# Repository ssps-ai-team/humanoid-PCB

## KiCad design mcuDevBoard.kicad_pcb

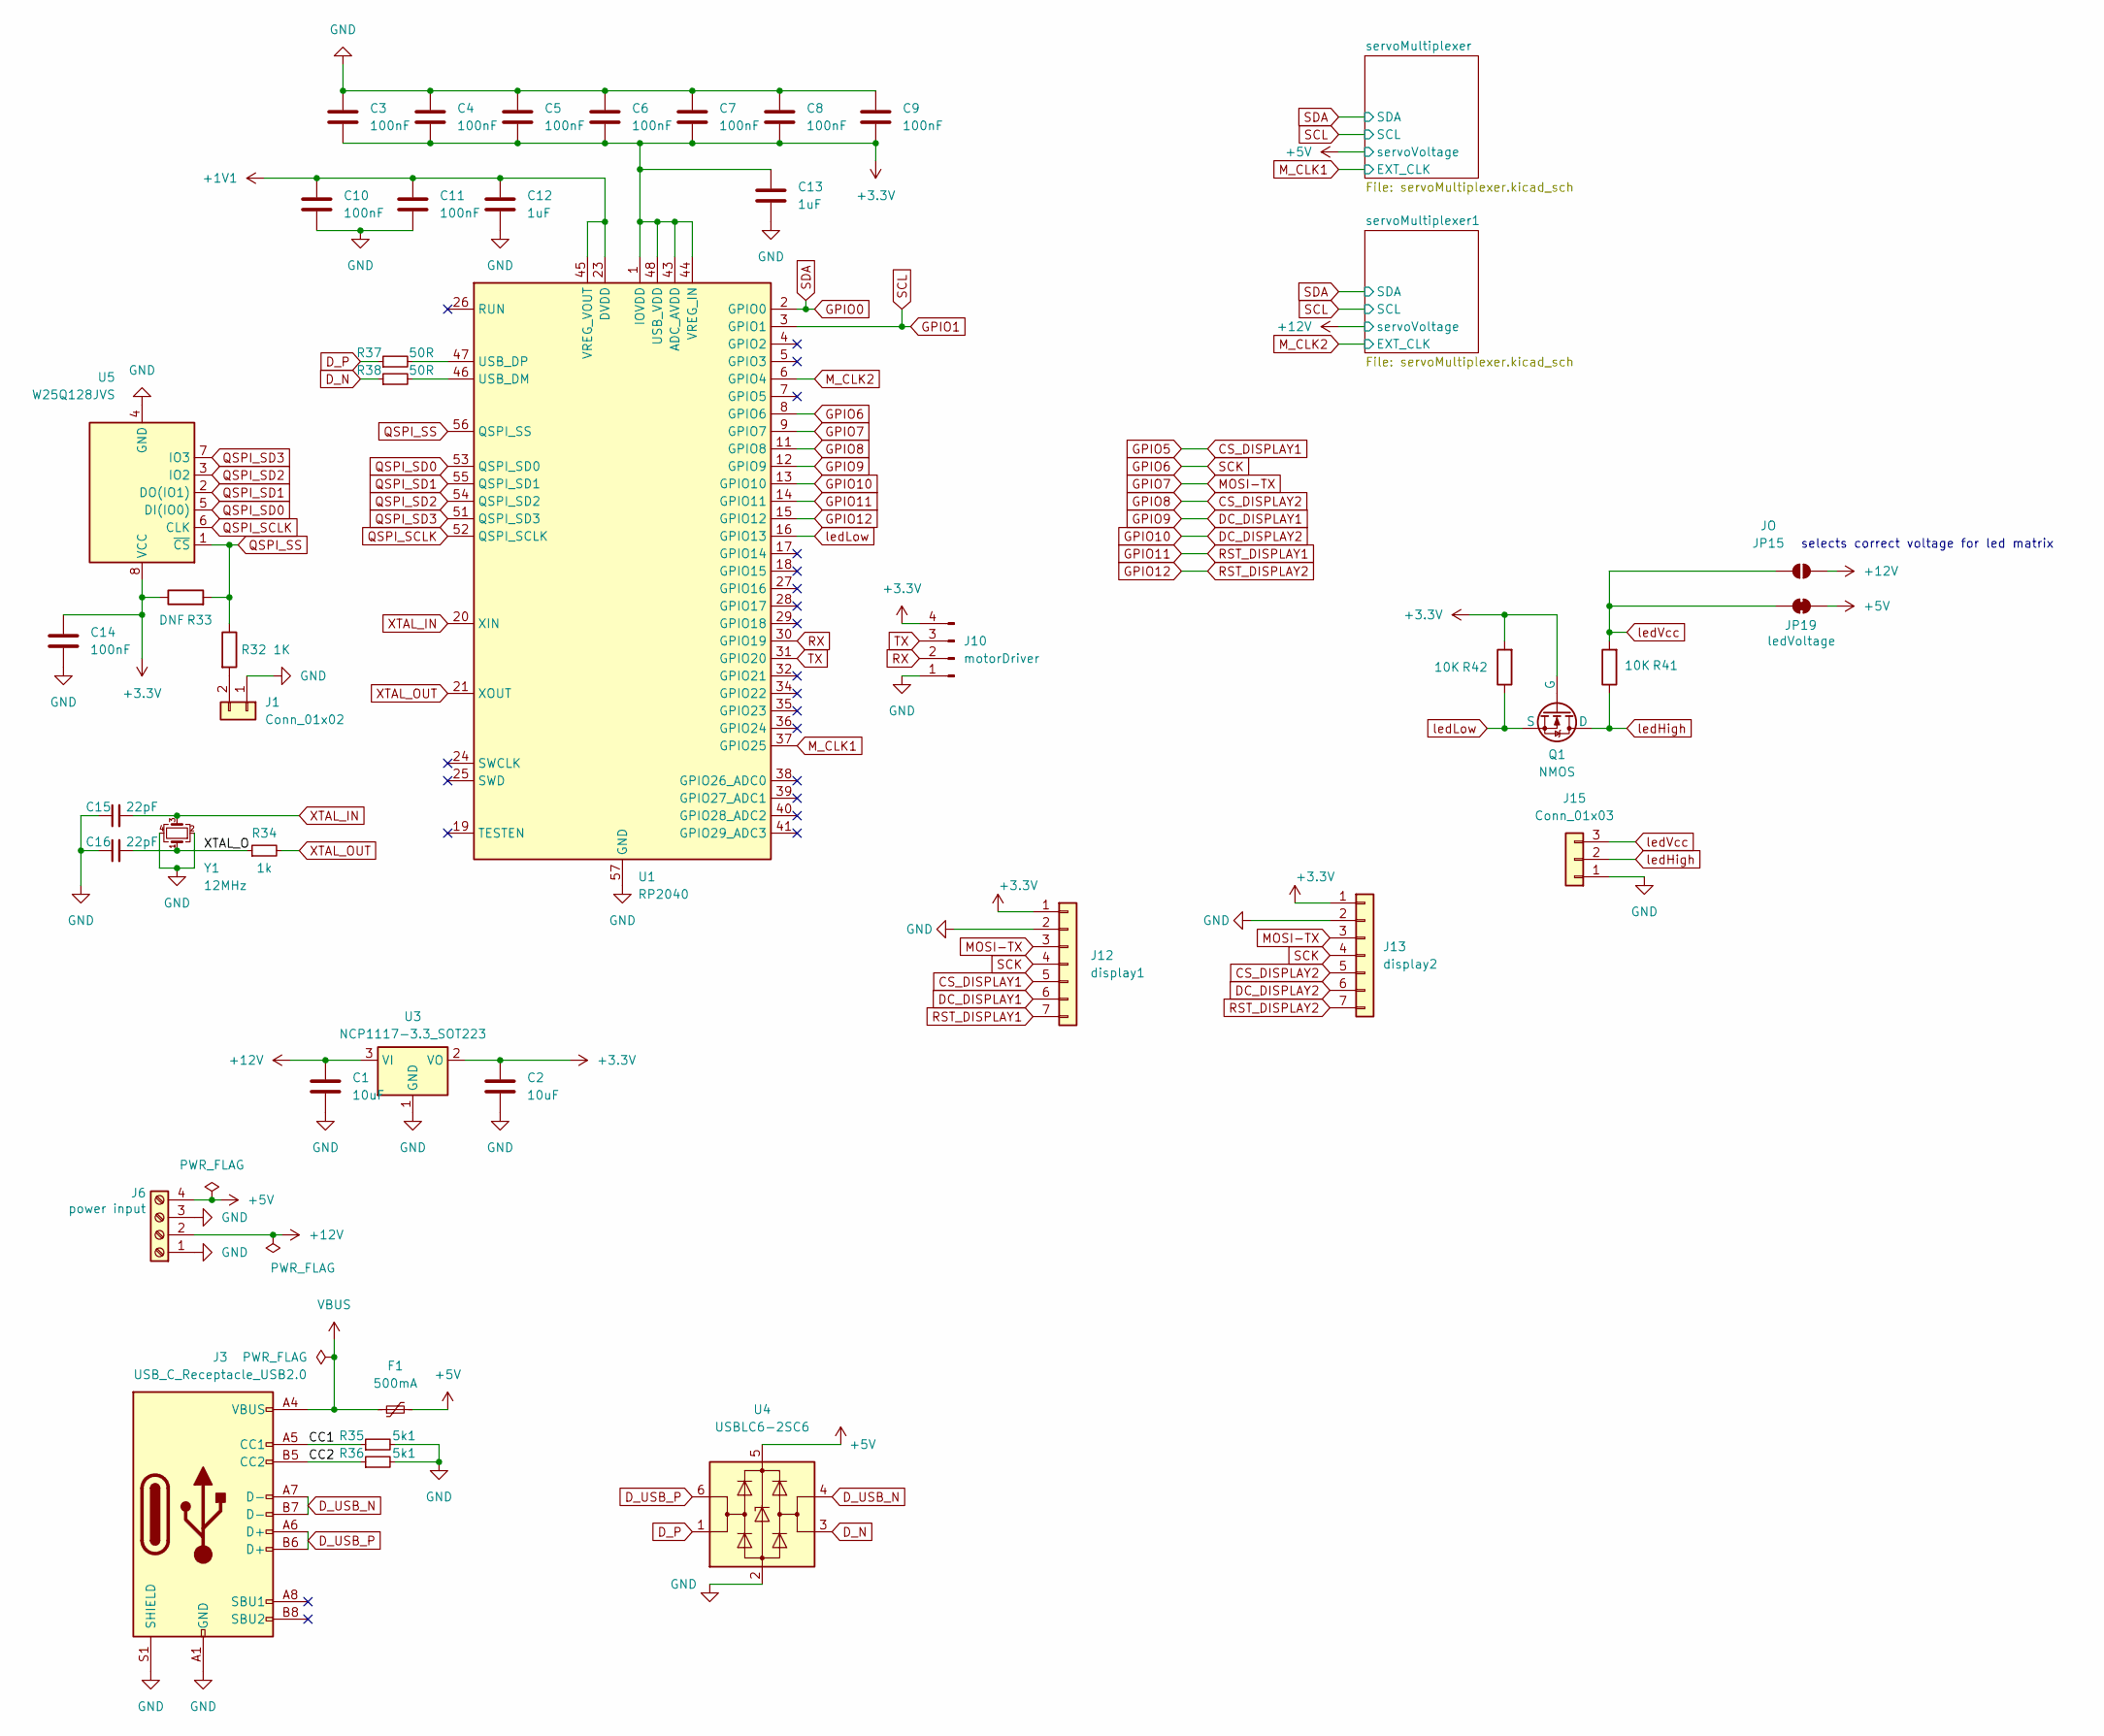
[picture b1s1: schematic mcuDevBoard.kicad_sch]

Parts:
C1, C2: 10uF; C_1206_3216Metric_Pad1.33x1.80mm_HandSolder
C3, C4, C5, C6, C7, C8, C9, C10, C11, C14: 100nF; C_0805_2012Metric_Pad1.18x1.45mm_HandSolder
C12, C13: 1uF; C_0805_2012Metric_Pad1.18x1.45mm_HandSolder
C15, C16: 22pF; C_0805_2012Metric_Pad1.18x1.45mm_HandSolder; LCSC C1555
F1: 500mA; Fuse_1206_3216Metric; LCSC C70076
J1: Conn_01x02; PinSocket_1x02_P2.54mm_Vertical
J3: USB_C_Receptacle_USB2.0; USB_C_Receptacle_HRO_TYPE-C-31-M-12; LCSC C165948
J6: power input; CONN-TH_4P-P7.50_DIBO_DB128V-7.5-4P-GN-S
J10: motorDriver; PinHeader_1x04_P2.54mm_Vertical
J12: display1; PinHeader_1x07_P2.54mm_Vertical
J13: display2; PinHeader_1x07_P2.54mm_Vertical
J15: Conn_01x03; PinSocket_1x03_P2.54mm_Vertical
JP15: JO; SolderJumper-2_P1.3mm_Open_RoundedPad1.0x1.5mm
JP19: ledVoltage; SolderJumper-2_P1.3mm_Bridged_RoundedPad1.0x1.5mm
Q1: NMOS; SOT-23_Handsoldering
R32: 1K; R_1206_3216Metric_Pad1.30x1.75mm_HandSolder
R33: DNF; R_1206_3216Metric_Pad1.30x1.75mm_HandSolder
R34: 1k; R_1206_3216Metric_Pad1.30x1.75mm_HandSolder; LCSC C11702
R35, R36: 5k1; R_1206_3216Metric_Pad1.30x1.75mm_HandSolder; LCSC C25905
R37, R38: 50R; C_0805_2012Metric; LCSC C25190
R41, R42: 10K; R_1206_3216Metric_Pad1.30x1.75mm_HandSolder
U1: RP2040; QFN-56-1EP_7x7mm_P0.4mm_EP3.2x3.2mm
U3: NCP1117-3.3_SOT223; SOT-223-3_TabPin2
U4: USBLC6-2SC6; SOT-23-6; LCSC C2827654
U5: W25Q128JVS; SOIC-8_5.23x5.23mm_P1.27mm
Y1: 12MHz; Crystal_SMD_3225-4Pin_3.2x2.5mm; LCSC C9002

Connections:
+1V1: C10.1, C11.1, C12.1, U1.23 (DVDD), U1.45 (VREG_VOUT), U1.50 (DVDD)
+3.3V: C2.1, C3.2, C4.2, C5.2, C6.2, C7.2, C8.2, C9.2, C13.1, C14.1, J10.4, J12.1, J13.1, Q1.2 (G), R33.1, R42.2, U1.1 (IOVDD), U1.10 (IOVDD), U1.22 (IOVDD), U1.33 (IOVDD), U1.42 (IOVDD), U1.43 (ADC_AVDD), U1.44 (VREG_IN), U1.48 (USB_VDD), U1.49 (IOVDD), U3.2 (VO), U5.8 (VCC); also elsewhere on the board
+5V: F1.2, J6.4, JP19.1 (A), U4.5 (VBUS); also elsewhere on the board
+12V: C1.1, J6.2, JP15.1 (A), U3.3 (VI); also elsewhere on the board
/CC1: J3.A5 (CC1), R35.1
/CC2: J3.B5 (CC2), R36.1
/XTAL_O: C16.2, R34.1, Y1.1
CS_DISPLAY1: J12.5
CS_DISPLAY2: J13.5, U1.11 (GPIO8)
DC_DISPLAY1: J12.6, U1.12 (GPIO9)
DC_DISPLAY2: J13.6, U1.13 (GPIO10)
D_N: R38.1, U4.3 (I/O2)
D_P: R37.1, U4.1 (I/O1)
D_USB_N: J3.A7 (D-), J3.B7 (D-), U4.4 (I/O2)
D_USB_P: J3.A6 (D+), J3.B6 (D+), U4.6 (I/O1)
GND: C1.2, C2.2, C3.1, C4.1, C5.1, C6.1, C7.1, C8.1, C9.1, C10.2, C11.2, C12.2, C13.2, C14.2, C15.1, C16.1, J1.1, J3.A1 (GND), J3.A12 (GND), J3.B1 (GND), J3.B12 (GND), J3.S1 (SHIELD), J6.1, J6.3, J10.1, J12.2, J13.2, J15.1, R35.2, R36.2, U1.57 (GND), U3.1 (GND), U4.2 (GND), U5.4 (GND), Y1.2, Y1.4; also elsewhere on the board
GPIO0: U1.2 (GPIO0); also elsewhere on the board
GPIO1: U1.3 (GPIO1); also elsewhere on the board
GPIO6: J12.4, J13.4, U1.8 (GPIO6)
GPIO7: J12.3, J13.3, U1.9 (GPIO7)
GPIO11: J12.7, U1.14 (GPIO11)
GPIO12: J13.7, U1.15 (GPIO12)
M_CLK1: U1.37 (GPIO25); also elsewhere on the board
M_CLK2: U1.6 (GPIO4); also elsewhere on the board
unnamed: J1.2, R32.2
unnamed: R38.2, U1.46 (USB_DM)
unnamed: R37.2, U1.47 (USB_DP)
QSPI_SCLK: U1.52 (QSPI_SCLK), U5.6 (CLK)
QSPI_SD0: U1.53 (QSPI_SD0), U5.5 (DI(IO0))
QSPI_SD1: U1.55 (QSPI_SD1), U5.2 (DO(IO1))
QSPI_SD2: U1.54 (QSPI_SD2), U5.3 (IO2)
QSPI_SD3: U1.51 (QSPI_SD3), U5.7 (IO3)
QSPI_SS: R32.1, R33.2, U1.56 (QSPI_SS), U5.1 (~CS)
RX: J10.2, U1.30 (GPIO19)
TX: J10.3, U1.31 (GPIO20)
VBUS: F1.1, J3.A4 (VBUS), J3.A9 (VBUS), J3.B4 (VBUS), J3.B9 (VBUS)
XTAL_IN: C15.2, U1.20 (XIN), Y1.3
XTAL_OUT: R34.2, U1.21 (XOUT)
ledHigh: J15.2, Q1.1 (D), R41.1
ledLow: Q1.3 (S), R42.1, U1.16 (GPIO13)
ledVcc: J15.3, JP15.2 (B), JP19.2 (B), R41.2

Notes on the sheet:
selects correct voltage for led matrix

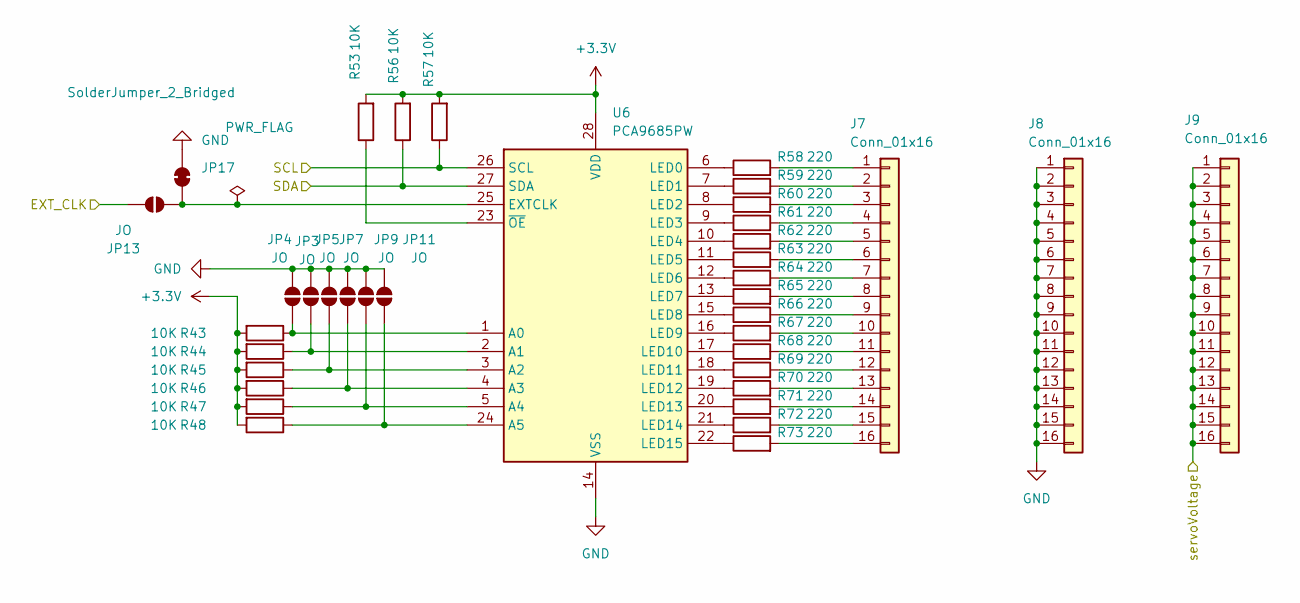
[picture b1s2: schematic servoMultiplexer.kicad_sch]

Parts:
J7, J8, J9: Conn_01x16; PinHeader_1x16_P2.54mm_Vertical
JP3, JP4, JP5, JP7, JP9, JP11, JP13: JO; SolderJumper-2_P1.3mm_Open_RoundedPad1.0x1.5mm
JP17: SolderJumper_2_Bridged; SolderJumper-2_P1.3mm_Bridged_RoundedPad1.0x1.5mm
R43, R44, R45, R46, R47, R48, R53, R56, R57: 10K; R_1206_3216Metric_Pad1.30x1.75mm_HandSolder
R58, R59, R60, R61, R62, R63, R64, R65, R66, R67, R68, R69, R70, R71, R72, R73: 220; R_1206_3216Metric_Pad1.30x1.75mm_HandSolder
U6: PCA9685PW; TSSOP-28_4.4x9.7mm_P0.65mm

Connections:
+3.3V: R43.2, R44.2, R45.2, R46.2, R47.2, R48.2, R53.2, R56.2, R57.2, U6.28 (VDD); also elsewhere on the board
+5V: J9.1, J9.2, J9.3, J9.4, J9.5, J9.6, J9.7, J9.8, J9.9, J9.10, J9.11, J9.12, J9.13, J9.14, J9.15, J9.16; also elsewhere on the board
GND: J8.1, J8.2, J8.3, J8.4, J8.5, J8.6, J8.7, J8.8, J8.9, J8.10, J8.11, J8.12, J8.13, J8.14, J8.15, J8.16, JP3.2 (B), JP4.2 (B), JP5.2 (B), JP7.2 (B), JP9.2 (B), JP11.2 (B), JP17.2 (B), U6.14 (VSS); also elsewhere on the board
GPIO0: R56.1, U6.27 (SDA); also elsewhere on the board
GPIO1: R57.1, U6.26 (SCL); also elsewhere on the board
M_CLK1: JP13.2 (B); also elsewhere on the board
unnamed: J7.1, R58.2
unnamed: J7.2, R59.2
unnamed: J7.3, R60.2
unnamed: J7.4, R61.2
unnamed: J7.5, R62.2
unnamed: J7.6, R63.2
unnamed: J7.7, R64.2
unnamed: J7.8, R65.2
unnamed: J7.9, R66.2
unnamed: J7.10, R67.2
unnamed: J7.11, R68.2
unnamed: J7.12, R69.2
unnamed: J7.13, R70.2
unnamed: J7.14, R71.2
unnamed: J7.15, R72.2
unnamed: J7.16, R73.2
unnamed: JP3.1 (A), R44.1, U6.2 (A1)
unnamed: JP4.1 (A), R43.1, U6.1 (A0)
unnamed: JP5.1 (A), R45.1, U6.3 (A2)
unnamed: JP7.1 (A), R46.1, U6.4 (A3)
unnamed: JP9.1 (A), R47.1, U6.5 (A4)
unnamed: JP11.1 (A), R48.1, U6.24 (A5)
unnamed: JP13.1 (A), JP17.1 (A), U6.25 (EXTCLK)
unnamed: R58.1, U6.6 (LED0)
unnamed: R59.1, U6.7 (LED1)
unnamed: R60.1, U6.8 (LED2)
unnamed: R61.1, U6.9 (LED3)
unnamed: R62.1, U6.10 (LED4)
unnamed: R63.1, U6.11 (LED5)
unnamed: R64.1, U6.12 (LED6)
unnamed: R65.1, U6.13 (LED7)
unnamed: R66.1, U6.15 (LED8)
unnamed: R67.1, U6.16 (LED9)
unnamed: R68.1, U6.17 (LED10)
unnamed: R69.1, U6.18 (LED11)
unnamed: R70.1, U6.19 (LED12)
unnamed: R71.1, U6.20 (LED13)
unnamed: R72.1, U6.21 (LED14)
unnamed: R73.1, U6.22 (LED15)
unnamed: R53.1, U6.23 (~OE)

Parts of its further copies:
J2, J4, J5: Conn_01x16; PinHeader_1x16_P2.54mm_Vertical
JP1, JP2, JP6, JP8, JP10, JP12, JP14: JO; SolderJumper-2_P1.3mm_Open_RoundedPad1.0x1.5mm
JP18: SolderJumper_2_Bridged; SolderJumper-2_P1.3mm_Bridged_RoundedPad1.0x1.5mm
R1, R2, R3, R4, R5, R6, R7, R8, R9: 10K; R_1206_3216Metric_Pad1.30x1.75mm_HandSolder
R10, R11, R12, R13, R14, R15, R16, R17, R18, R19, R20, R21, R22, R23, R24, R25: 220; R_1206_3216Metric_Pad1.30x1.75mm_HandSolder
U2: PCA9685PW; TSSOP-28_4.4x9.7mm_P0.65mm

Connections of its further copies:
+3.3V: R1.2, R2.2, R3.2, R4.2, R5.2, R6.2, R7.2, R8.2, R9.2, U2.28 (VDD); also elsewhere on the board
+12V: J5.1, J5.2, J5.3, J5.4, J5.5, J5.6, J5.7, J5.8, J5.9, J5.10, J5.11, J5.12, J5.13, J5.14, J5.15, J5.16; also elsewhere on the board
GND: J4.1, J4.2, J4.3, J4.4, J4.5, J4.6, J4.7, J4.8, J4.9, J4.10, J4.11, J4.12, J4.13, J4.14, J4.15, J4.16, JP1.2 (B), JP2.2 (B), JP6.2 (B), JP8.2 (B), JP10.2 (B), JP12.2 (B), JP18.2 (B), U2.14 (VSS); also elsewhere on the board
GPIO0: R8.1, U2.27 (SDA); also elsewhere on the board
GPIO1: R9.1, U2.26 (SCL); also elsewhere on the board
M_CLK2: JP14.2 (B); also elsewhere on the board
unnamed: J2.1, R10.2
unnamed: J2.2, R11.2
unnamed: J2.3, R12.2
unnamed: J2.4, R13.2
unnamed: J2.5, R14.2
unnamed: J2.6, R15.2
unnamed: J2.7, R16.2
unnamed: J2.8, R17.2
unnamed: J2.9, R18.2
unnamed: J2.10, R19.2
unnamed: J2.11, R20.2
unnamed: J2.12, R21.2
unnamed: J2.13, R22.2
unnamed: J2.14, R23.2
unnamed: J2.15, R24.2
unnamed: J2.16, R25.2
unnamed: JP1.1 (A), R1.1, U2.1 (A0)
unnamed: JP2.1 (A), R2.1, U2.2 (A1)
unnamed: JP6.1 (A), R3.1, U2.3 (A2)
unnamed: JP8.1 (A), R4.1, U2.4 (A3)
unnamed: JP10.1 (A), R5.1, U2.5 (A4)
unnamed: JP12.1 (A), R6.1, U2.24 (A5)
unnamed: JP14.1 (A), JP18.1 (A), U2.25 (EXTCLK)
unnamed: R10.1, U2.6 (LED0)
unnamed: R11.1, U2.7 (LED1)
unnamed: R12.1, U2.8 (LED2)
unnamed: R13.1, U2.9 (LED3)
unnamed: R14.1, U2.10 (LED4)
unnamed: R15.1, U2.11 (LED5)
unnamed: R16.1, U2.12 (LED6)
unnamed: R17.1, U2.13 (LED7)
unnamed: R18.1, U2.15 (LED8)
unnamed: R19.1, U2.16 (LED9)
unnamed: R20.1, U2.17 (LED10)
unnamed: R21.1, U2.18 (LED11)
unnamed: R22.1, U2.19 (LED12)
unnamed: R23.1, U2.20 (LED13)
unnamed: R24.1, U2.21 (LED14)
unnamed: R25.1, U2.22 (LED15)
unnamed: R7.1, U2.23 (~OE)

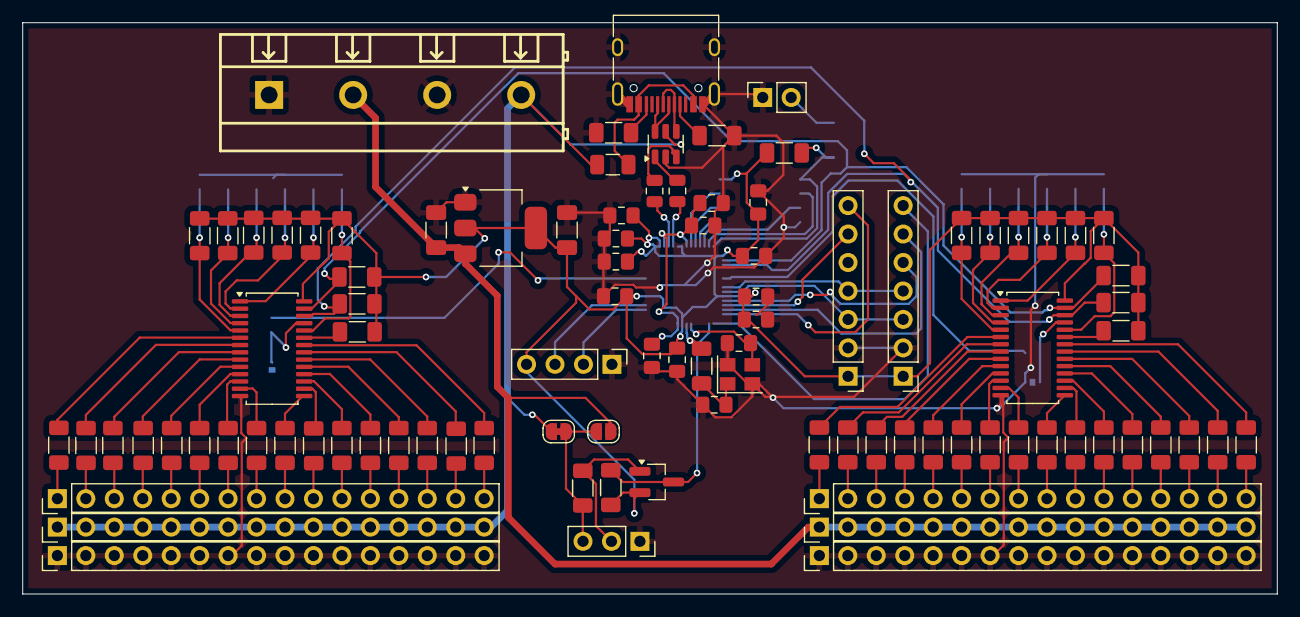
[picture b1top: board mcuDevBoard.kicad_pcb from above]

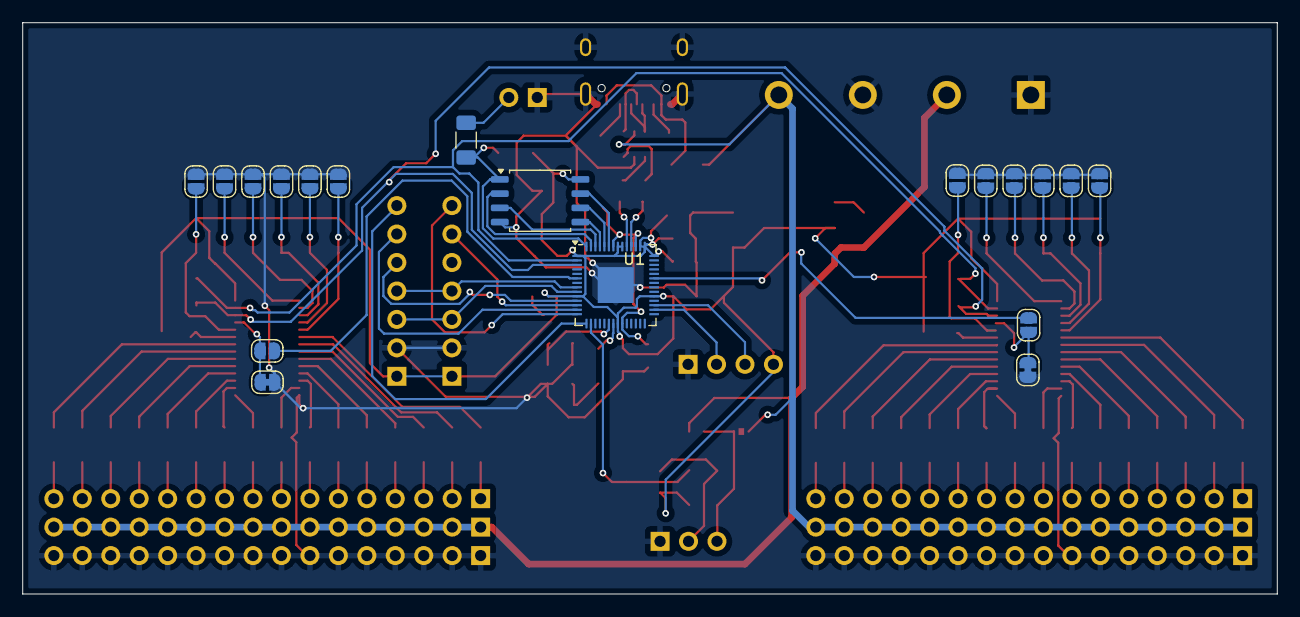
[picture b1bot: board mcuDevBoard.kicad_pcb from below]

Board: 2 copper layers, 112.0 x 51.0 mm, 115 parts (19 on the bottom side), 120 nets.

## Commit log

2024-12-10 base version
2025-03-06 pcb v0.2
